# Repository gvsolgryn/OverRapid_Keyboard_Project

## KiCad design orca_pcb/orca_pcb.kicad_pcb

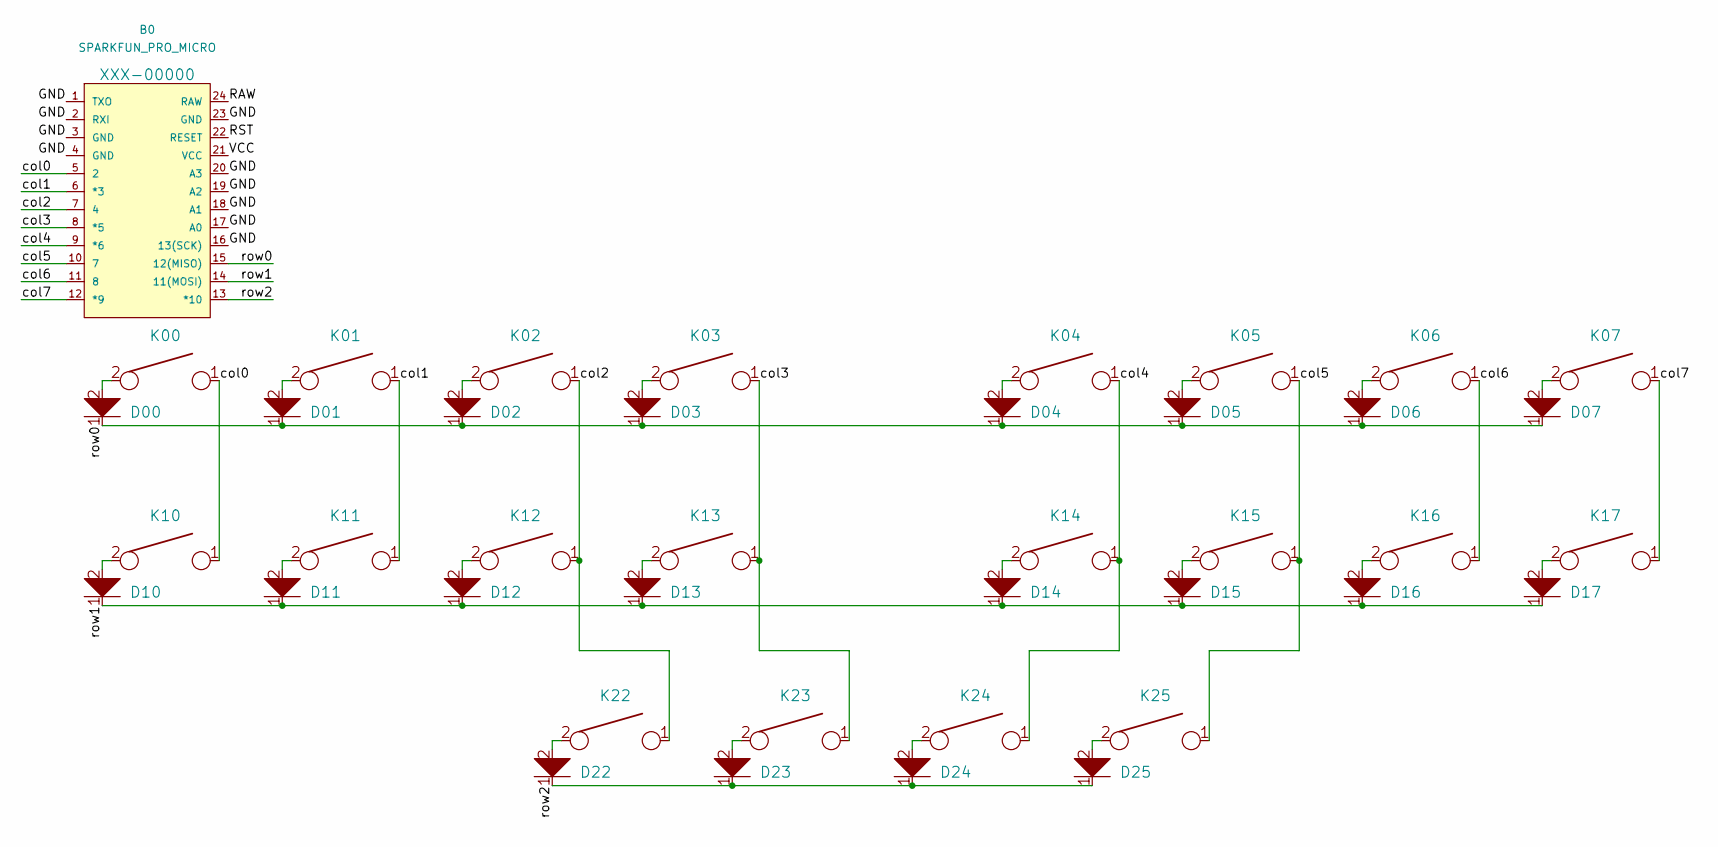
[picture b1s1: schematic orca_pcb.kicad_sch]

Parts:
B0: SPARKFUN_PRO_MICRO
D00, D01, D02, D03, D04, D05, D06, D07, D10, D11, D12, D13, D14, D15, D16, D17, D22, D23, D24, D25: D; D_SOD123_axial
K00, K01, K02, K03, K04, K05, K06, K07, K10, K11, K12, K13, K14, K15, K16, K17: KEYSW; SW_Cherry_MX_PCB_1.00u
K22, K23, K24, K25: KEYSW; SW_Cherry_MX_PCB_1.25u

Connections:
/GND: B0.1 (TXO), B0.2 (RXI), B0.3 (GND), B0.4 (GND), B0.16 (13(SCK)), B0.17 (A0), B0.18 (A1), B0.19 (A2), B0.20 (A3), B0.23 (GND)
/RAW: B0.24 (RAW)
/RST: B0.22 (RESET)
/VCC: B0.21 (VCC)
/col0: B0.5 (2), K00.1, K10.1
/col1: B0.6 (*3), K01.1, K11.1
/col2: B0.7 (4), K02.1, K12.1, K22.1
/col3: B0.8 (*5), K03.1, K13.1, K23.1
/col4: B0.9 (*6), K04.1, K14.1, K24.1
/col5: B0.10 (7), K05.1, K15.1, K25.1
/col6: B0.11 (8), K06.1, K16.1
/col7: B0.12 (*9), K07.1, K17.1
/row0: B0.15 (12(MISO)), D00.1, D01.1, D02.1, D03.1, D04.1, D05.1, D06.1, D07.1
/row1: B0.14 (11(MOSI)), D10.1, D11.1, D12.1, D13.1, D14.1, D15.1, D16.1, D17.1
/row2: B0.13 (*10), D22.1, D23.1, D24.1, D25.1
unnamed: D00.2, K00.2
unnamed: D01.2, K01.2
unnamed: D02.2, K02.2
unnamed: D03.2, K03.2
unnamed: D04.2, K04.2
unnamed: D05.2, K05.2
unnamed: D06.2, K06.2
unnamed: D07.2, K07.2
unnamed: D10.2, K10.2
unnamed: D11.2, K11.2
unnamed: D12.2, K12.2
unnamed: D13.2, K13.2
unnamed: D14.2, K14.2
unnamed: D15.2, K15.2
unnamed: D16.2, K16.2
unnamed: D17.2, K17.2
unnamed: D22.2, K22.2
unnamed: D23.2, K23.2
unnamed: D24.2, K24.2
unnamed: D25.2, K25.2

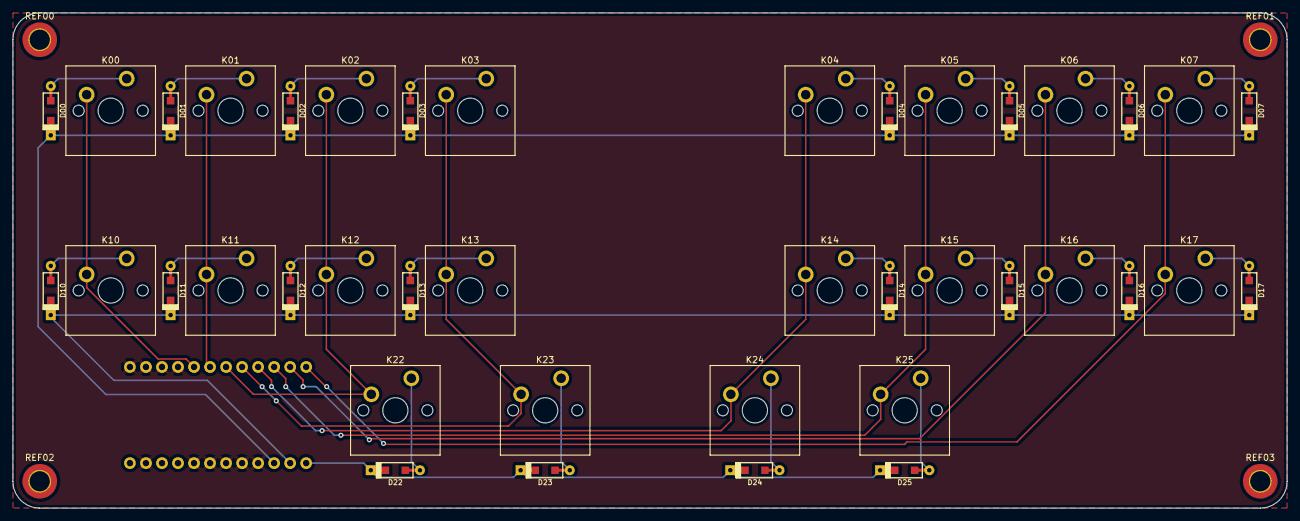
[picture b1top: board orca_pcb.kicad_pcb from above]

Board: 2 copper layers, 202.0 x 78.5 mm, 45 parts (1 on the bottom side), 32 nets.

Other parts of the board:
REF00, REF01, REF02, REF03: MountingHole_3.2mm_M3_ISO14580_Pad_TopOnly

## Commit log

2021-09-01 gitignore 추가
2021-09-01 개선판 v2 업로드
2021-10-14 Add Size DWG for KiCad & Create PCB
2021-10-14 Create gerber file
2021-10-14 Add QMK Firmware Keymap
2021-10-17 create version2
2022-01-10 PCB V3 및 KiCad6.0 버전 업글
